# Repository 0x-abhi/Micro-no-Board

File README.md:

# Micro-no Board (µNO Board)- An Open Source Arduino-Compatible Development Platform

Welcome to the official documentation for the **µNO Board** (pronounced "Micro-no Board"). This open-source project presents a minimalistic, hardware-level implementation of the popular Arduino Uno, centered around the **ATmega328P-PU** microcontroller. Engineered and documented by **Abhishek Tomar**, this project is a comprehensive platform for electronics students and embedded systems learners seeking to understand the internal architecture and design of a microcontroller development board.

---

## 📚 Table of Contents

1. [Project Overview](#project-overview)
2. [Technical Features](#technical-features)
3. [Detailed Schematic Breakdown](#detailed-schematic-breakdown)

   * [Power Supply Circuit](#power-supply-circuit)
   * [Microcontroller Core](#microcontroller-core)
   * [Oscillator Configuration](#oscillator-configuration)
   * [Reset Mechanism](#reset-mechanism)
   * [FTDI Serial Programming Header](#ftdi-serial-programming-header)
   * [ISP Bootloader Interface](#isp-bootloader-interface)
   * [Status LED Indicator](#status-led-indicator)
4. [Arduino to ATmega328P Pin Mapping](#arduino-to-atmega328p-pin-mapping)
5. [Burning the Bootloader](#burning-the-bootloader)
6. [Uploading Programs via FTDI](#uploading-programs-via-ftdi)
7. [Understanding ISP and FTDI Protocols](#understanding-isp-and-ftdi-protocols)
8. [Accessing Design Files](#accessing-design-files)
9. [Contributions and Collaboration](#contributions-and-collaboration)
10. [License](#license)

---

## 🔍 Project Overview

The **µNO Board** replicates the functionality of the Arduino Uno but strips it to its essentials. Rather than relying on a premade Arduino module, this project demonstrates the discrete components necessary to build a fully functional development board from the ground up:

* Power regulation and filtering
* Stable clock generation
* GPIO and ADC decoupling
* Reset and auto-reset mechanisms
* Programming via serial (FTDI) or SPI (ISP)

It serves as both a learning tool and a production-ready embedded platform.

---

## ⚙️ Technical Features

* **Microcontroller**: ATmega328P-PU (8-bit AVR RISC architecture)
* **Voltage Regulation**: AMS1117-5.0V LDO regulator
* **System Clock**: External 16 MHz crystal
* **Programming Interfaces**: FTDI (UART) and ISP (SPI)
* **Manual Reset Button**: Physical switch for hardware resets
* **Input Voltage Range**: 6V to 15V (via VIN pin)
* **Regulated Output**: +5V for MCU and peripherals
* **GPIO Access**: Digital pins D0-D13, Analog pins A0-A5
* **Status Indicator**: Onboard LED that Indicates power ON/OFF

---

## 🔧 Detailed Schematic Breakdown

### 🔌 Power Supply Circuit

* **AMS1117-5.0V Regulator (U2)**

  * Converts input voltage (up to 15V) to 5V regulated output.
  * Essential for powering the MCU and peripherals.
* **Input/Output Capacitors**:

  * **C7, C8 (10uF)**: Stabilize input (VIN) and output (VOUT).
  * Filter transient fluctuations and reduce switching noise.

### 🧠 Microcontroller Core (ATmega328P)

* **Power Pins**:

  * **VCC (Pin 7)**: Main power input
  * **AVCC (Pin 20)**: Power supply for the ADC block
  * **GND (Pins 8 & 22)**: Common ground
* **Bypass Capacitors**:

  * **C3, C4, C6 (100nF)**: Placed near VCC and AVCC to suppress high-frequency noise.

### ⏱️ Oscillator Configuration

* **Crystal Oscillator (Y1, 16 MHz)**

  * External clock source for the MCU, ensures stable system timing
* **Load Capacitors (C1, C2 = 22pF)**

  * Ensure proper startup and oscillation of the crystal

### 🔁 Reset Mechanism

* **R1 (10kΩ)**: Pull-up resistor on RESET pin
* **SW1**: Push-button reset (pulls RESET to GND when pressed)
* **C5 (100nF)**: Coupled with FTDI DTR pin for auto-reset during code upload

### 🔄 FTDI Serial Programming Header (J5)

* **6-pin Header**: GND, VCC, RX, TX, DTR, CTS
* **Function**: Enables uploading sketches via UART after bootloader is flashed
* **Connection Tip**: Ensure TX (FTDI) connects to RX (MCU) and vice versa

### 💾 ISP Bootloader Interface (J1)

* **Standard 6-pin ISP Header**

  * MISO, MOSI, SCK, RESET, VCC, GND
* **Purpose**: Used for flashing the bootloader or burning hex files directly via SPI

---

## 🧩 Arduino to ATmega328P Pin Mapping

| Arduino | ATmega328P Pin | Port    | Description      |
| ------- | -------------- | ------- | ---------------- |
| D0      | 2              | PD0     | UART RX          |
| D1      | 3              | PD1     | UART TX          |
| D2-D7   | 4-9            | PD2-PD7 | Digital I/O      |
| D8-D13  | 14-19          | PB0-PB5 | SPI & I/O        |
| A0-A5   | 23-28          | PC0-PC5 | ADC & I2C        |
| RESET   | 1              | PC6     | System Reset     |
| AREF    | 21             | -       | Analog Reference |

---

## 🔥 Burning the Bootloader

### 💡 What is a Bootloader?

A bootloader is a small program that resides in the MCU’s flash memory, allowing firmware to be uploaded via UART rather than ISP.

### 🔧 Required Tools

* USBasp Programmer or Arduino-as-ISP

### 🧭 Step-by-Step Guide

1. Connect the ISP header on the board to your programmer.
2. Launch Arduino IDE.
3. Go to **Tools > Board > Arduino Uno**.
4. Under **Programmer**, select **USBasp** (or Arduino as ISP).
5. Click **Burn Bootloader**.

Once burned, your microcontroller can now be programmed through FTDI.

---

## ⬆️ Uploading Programs via FTDI

### 🛠️ Required Hardware

* FTDI USB-to-Serial Converter

### Wiring:

* FTDI TX → MCU RX
* FTDI RX → MCU TX
* DTR → RESET (via 100nF capacitor)
* VCC, GND connected properly

### Upload Steps:

1. Open Arduino IDE and select **Arduino Uno** as the board.
2. Choose the correct **COM Port**.
3. Click **Upload**.

The auto-reset circuit will handle entry into the bootloader automatically.

---

## 🧠 Understanding ISP and FTDI Protocols

### ISP (In-System Programming)

* **Protocol**: SPI-based (MOSI, MISO, SCK)
* **Use Case**: Burning bootloaders or uploading compiled firmware directly
* **Requires**: External programmer

### FTDI (USB-to-UART)

* **Protocol**: UART-based (TX/RX)
* **Use Case**: Uploading code to bootloaded MCUs
* **Advantage**: No extra hardware once bootloader is installed

---
## 🔮 Future Improvements and Expansion Ideas

As a learning platform and minimal Arduino-compatible board, the µNO Board has room for useful upgrades. Here are some potential enhancements that could improve its functionality, usability, and professional quality:

### 🔧 Hardware Improvements

- **⚡ Onboard USB-to-Serial (FTDI)**  
  Add a built-in CH340 or CP2102 IC for USB programming, eliminating the need for an external FTDI adapter.

- **🔋 3.3V Voltage Regulator**  
  Add an LDO regulator (e.g., AMS1117-3.3V) to support 3.3V sensors or modules on the same board.

- **🛡️ Reverse Polarity Protection**  
  Include a Schottky diode or P-MOSFET to protect the board from accidental reverse voltage input.

- **🧲 TVS Diodes or ESD Protection**  
  Protect sensitive GPIOs and the USB interface from electrostatic discharge or voltage spikes.

- **📦 Mounting Hole Grounding**  
  Connect metal mounting holes to GND for improved shielding and mechanical stability.

- **🧠 Additional GPIO Headers / Expansion Ports**  
  Break out I2C, SPI, ADC, and power lines to dedicated connectors for sensor/module expansion.

---

### 🖥️ Firmware & Bootloader Enhancements

- **⏱️ Optiboot Bootloader**  
  Use the smaller Optiboot variant to save flash memory and enable faster serial uploads (up to 115200 baud).

- **🧩 Arduino Board Package Support**  
  Create a custom board definition file (`boards.txt`) to add µNO as an official option in the Arduino IDE.

---

These enhancements can transform the µNO Board from a minimalist learning tool into a feature-rich, professional-grade embedded system. Explore, experiment, and evolve your design! 🚀

---

## 📁 Accessing Design Files

Your repository includes the following:

* `KiCad/`: Schematic and PCB design files
* `Gerber/`: Fabrication-ready output files
* `3D_Images/`: Visual renders of the board
* `README.md`: This documentation

📸 Board Images:

* 
* 
* 

---

## 🤝 Contributions and Collaboration

Contributions are welcome! Feel free to fork the repository, submit pull requests, or raise issues for bugs, suggestions, or improvements.

---

## 📜 License

This project is licensed under the **CERN-OHL-S v2** open hardware license. This ensures:

* Freedom to study, modify, manufacture, and distribute
* Requirement to share changes under the same license

---

❤️ Created with passion by Abhishek Tomar — Just a learner like you.

🌟 **Support This Project!**

If this project helped you learn, build, or get inspired, please ⭐ star the repository and share it!

Together, we make open hardware accessible and empowering for all. 💪✨

Happy Hacking 🚀

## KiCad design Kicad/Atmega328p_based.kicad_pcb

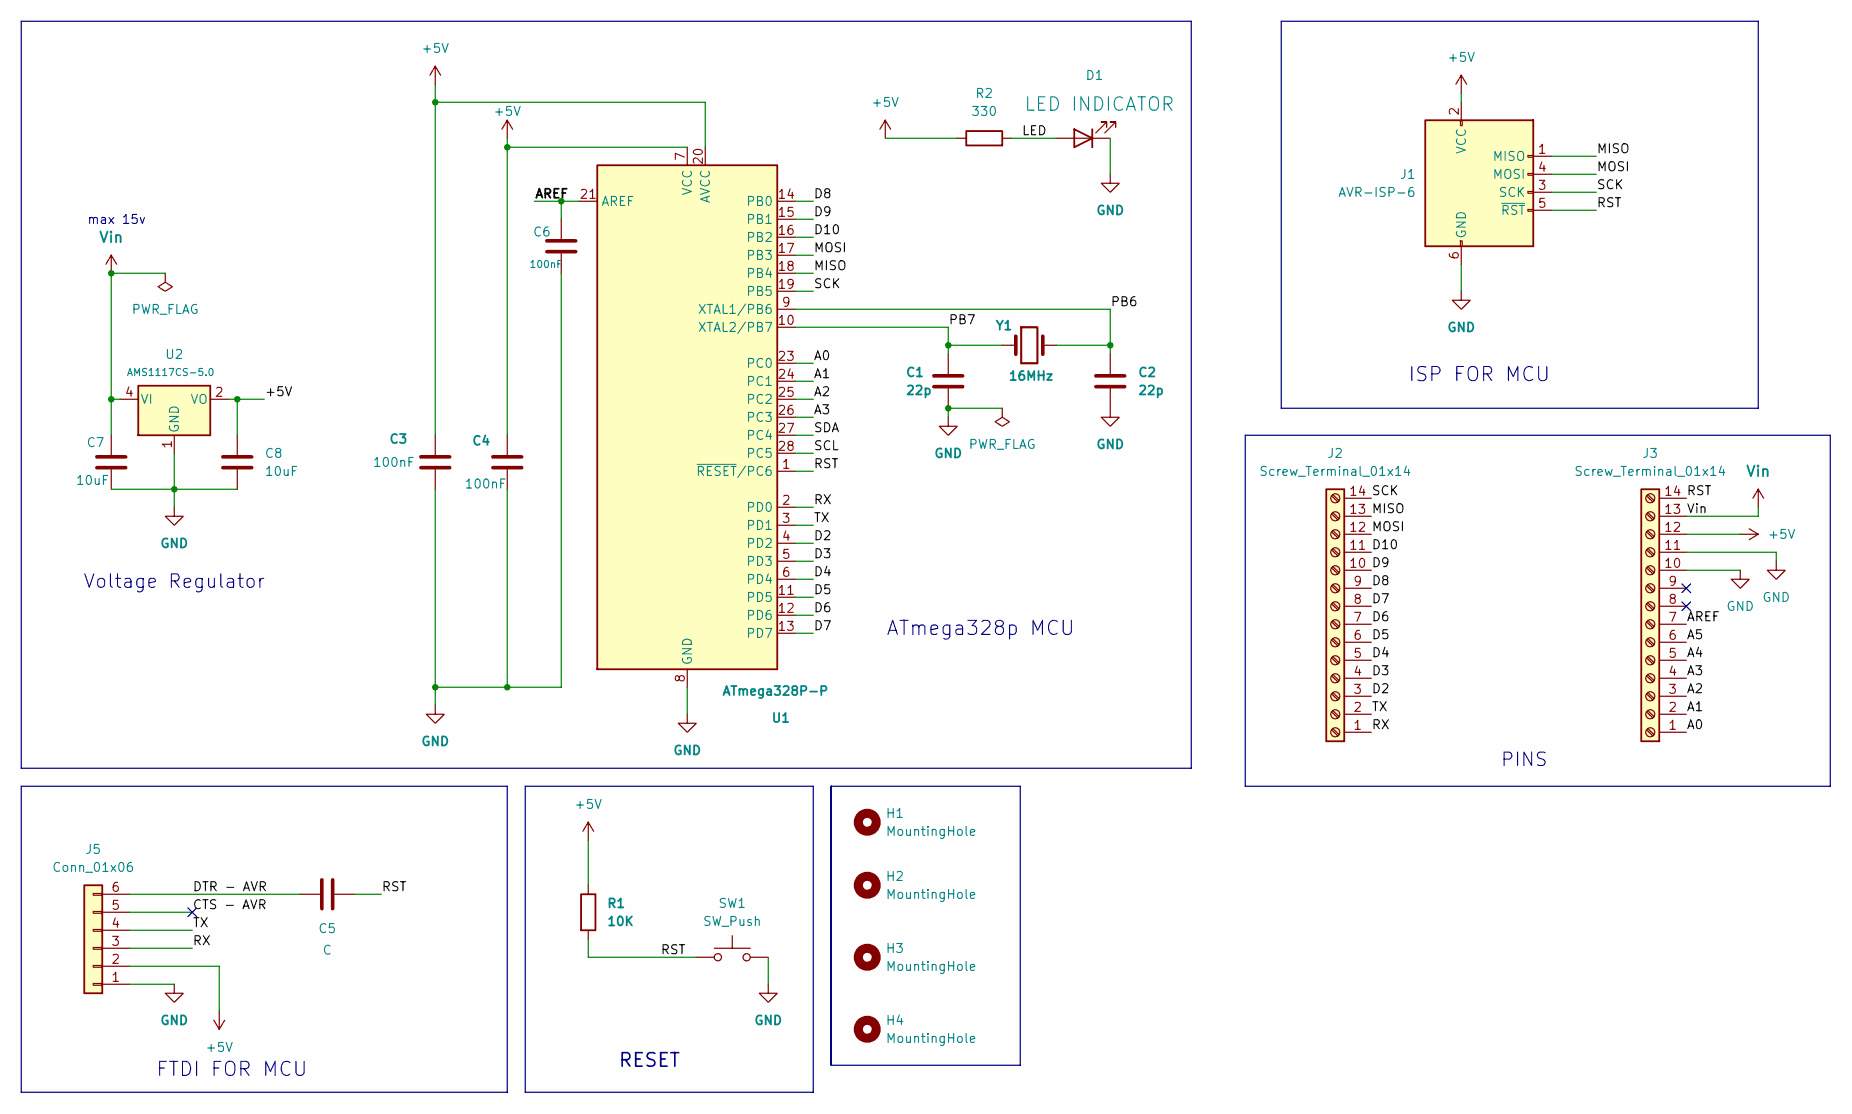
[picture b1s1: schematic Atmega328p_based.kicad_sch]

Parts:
C1, C2: 22p; C_0805_2012Metric
C3, C4, C6: 100nF; C_0805_2012Metric
C5: C; C_0805_2012Metric
C7, C8: 10uF; C_0805_2012Metric
D1: LED INDICATOR; LED_1206_3216Metric_Pad1.42x1.75mm_HandSolder
H1, H2, H3, H4: MountingHole; MountingHole_2.2mm_M2
J1: AVR-ISP-6; PinHeader_1x06_P2.54mm_Vertical
J2, J3: Screw_Terminal_01x14; PinHeader_1x14_P2.54mm_Vertical
J5: Conn_01x06; PinHeader_1x06_P2.54mm_Vertical
R1: 10K; R_0805_2012Metric
R2: 330; R_0805_2012Metric
SW1: SW_Push; SW_PUSH_6mm
U1: ATmega328P-P; DIP-28_W7.62mm
U2: AMS1117CS-5.0; SOIC-8_3.9x4.9mm_P1.27mm
Y1: 16MHz; Crystal_HC49-4H_Vertical

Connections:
+5V: C3.1, C4.1, C8.1, J1.2 (VCC), J3.12, J5.2, R1.1, R2.1, U1.7 (VCC), U1.20 (AVCC), U2.2 (VO), U2.3 (VO), U2.6 (VO), U2.7 (VO)
/ MOSI: J1.4 (MOSI), J2.12, U1.17 (PB3)
/A0: J3.1, U1.23 (PC0)
/A1: J3.2, U1.24 (PC1)
/A2: J3.3, U1.25 (PC2)
/A3: J3.4, U1.26 (PC3)
/A4: J3.5
/A5: J3.6
/AREF: C6.2, J3.7, U1.21 (AREF)
/CTS - AVR: J5.5
/D2: J2.3, U1.4 (PD2)
/D3: J2.4, U1.5 (PD3)
/D4: J2.5, U1.6 (PD4)
/D5: J2.6, U1.11 (PD5)
/D6: J2.7, U1.12 (PD6)
/D7: J2.8, U1.13 (PD7)
/D8: J2.9, U1.14 (PB0)
/D9: J2.10, U1.15 (PB1)
/D10: J2.11, U1.16 (PB2)
/DTR - AVR: C5.2, J5.6
/LED: D1.2 (A), R2.2
/PB6: C2.1, U1.9 (XTAL1/PB6), Y1.2
/PB7: C1.1, U1.10 (XTAL2/PB7), Y1.1
/RST: C5.1, J1.5 (~RST), J3.14, R1.2, SW1.1, U1.1 (~RESET/PC6)
/RX: J2.1, J5.3, U1.2 (PD0)
/SCK: J1.3 (SCK), J2.14, U1.19 (PB5)
/SCL: U1.28 (PC5)
/SDA: U1.27 (PC4)
/TX: J2.2, J5.4, U1.3 (PD1)
GND: C1.2, C2.2, C3.2, C4.2, C6.1, C7.2, C8.2, D1.1 (K), J1.6 (GND), J3.10, J3.11, J5.1, SW1.2, U1.8 (GND), U1.22 (GND), U2.1 (GND)
Vin: C7.1, J3.13, U2.4 (VI)

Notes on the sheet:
ATmega328p MCU
max 15v
FTDI FOR MCU
RESET
ISP FOR MCU
PINS
Voltage Regulator

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
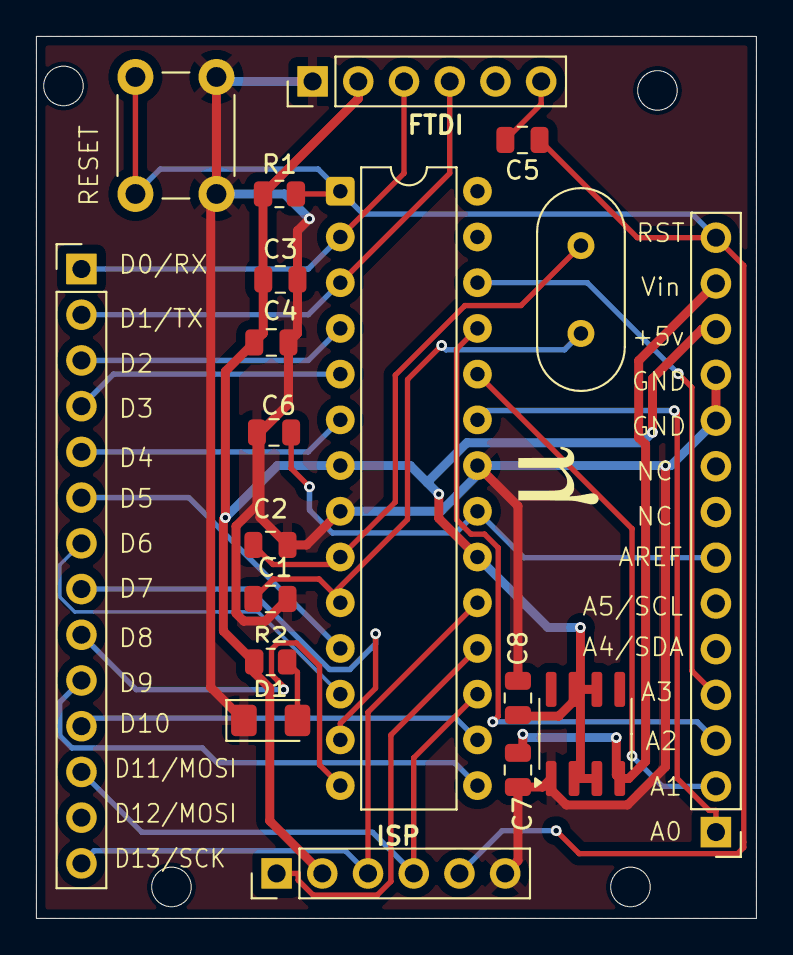
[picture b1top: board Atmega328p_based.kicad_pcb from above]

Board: 2 copper layers, 40.0 x 49.0 mm, 23 parts (0 on the bottom side), 27 nets.

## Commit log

2025-07-07 Initial commit: Micro-no Board (KiCad + Gerber + 3D + Docs)
